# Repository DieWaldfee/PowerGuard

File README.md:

# PowerGuard
PowerGuard-Platine und Software zur Sicherheitsüberwachung einer Heizstabsteuerung

**zugehörige Repositories**<br>
- PowerGuard (dieses Repository)
- Heizstabsteuerung (Steuerungsplatine <a href="https://github.com/DieWaldfee/Heizstabsteuerung"> Link </a>)
- Heizstab_ioBroker (Ansteuerungs-Blockly - ein MQTT-Broker wird benötigt - Link)

**Funktion:** <br>
Der ESP32 steuert 2 Temperatursensoren (DS18B20) an und liest diese aus. Die beiden Sensoren sollen am höchsten Punkt des Pufferspeichers der Heizung angebracht werden, in dem auch der elektrische Heizstab eingeschraubt ist. 
Die beiden Werte werden einerseits verglichen und andererseits benutzt, um die Pufferspeichertemperatur zu überwachen. Liegt die Temperatur zu hoch, dann ist zu viel Energie im Pufferspeicher und vermutlich ist der Heizstab dafür ursächlich -> der Heizstabsteuerung wird der Strom abgeschalten. Dies stellt eine unabhängige Sicherungsfunktion dar, das jedweder Fehler im Heizstabsystem behandelt und die Anlage in den sicheren Zustand überführt (d.h. aus).<p>
Der PowerGuard hat 2 Möglichkeiten dies zu tun: <br>
(1) die 5V Versorgung des ESP32 der Heizstabsteuerung abzuschalten -> die Relais werden nicht mehr angesteuert - unabhängig vom Fehlerbild. <br>
(2) die 12V Versorgungsspannung der Lastschaltrelais (SSR siehe Heizstabsteuerung) wird abgeschaltet -> die Heizstabsteuerung bleibt aktiv, kann aber nichts mehr schalten. <p>
Die Kommunikation mit dem ESP32 wird über WiFi abgewickelt und über das Protokoll MQTT umgesetzt. Es stehen mehrere Befehle zur Verfügung, die ebenfalls via MQTT an den ESP gesendet werden kann. Neben "restart" / "reboot" (führt zu einem Neustart des ESP32) kann die ganze Konfiguration und der debug-Level angepasst werden. Alle Anpassungen sind nach einem Neustart verloren, da diese nicht permanent gespeichert werden. Befehle werden unter der MQTT-Hierarchie in folgendem Ort empfangen: `SmartHome/Keller/Heizung/ESP32_PowerGuard/command` (MQTT_SERIAL_RECEIVER_COMMAND)

**Entwicklungsumgebungen:** <br>
Die aktuelle Software (V2.x) für den ESP32 wird mit **PlatformIO** entwickelt (z. B. in VS Code mit dem PlatformIO-Plugin). Die Konfiguration des Projekts befindet sich in der Datei `platformio.ini`; Compilieren und Flashen erfolgen direkt über PlatformIO.<br>
Die historische Erstversion (V1.0) wurde in der **Arduino-IDE** erstellt und ist im Unterordner `V1.0/` archiviert.<br>
Die Platine (PCB) habe ich in Eagle von AutoCAD modelliert. Für Maker gibt es eine kostenfreie Version. Die CAM-Daten (PCB-Produktionsdaten), sowie die BOM (Stückliste) sind ebenfalls aus Eagle ausgegeben.
Eine Übersichtsversion der Platine ist mit Fritzing umgesetzt und enthält auch einige Notizen zur Pinbelegung.<br>

**benötigte Umgebung:** <br>
- ioBroker zur Ansteuerung (geht natürlich auch mit anderen SmartHome-Systemen, solange diese MQTT sprechen können)
- ioBroker MGTT-Adapter
- MQTT-Broker: z.B. mosquitto unter Linux/Debian/Raspian...
- 230V Stromversorgung oder alternativ eine 5V Versorgung über z.B. ein USB-Ladegerät (muss 2 ESP32 sicher versorgen können -> 2A reicht völlig aus) oder über die Schraubklemmen anderweitig versorgt.

### Abhängigkeiten (PlatformIO / `platformio.ini`):
OneWire:_______________PaulStoffregen/OneWire (git-master) – v2.3.7 inkompatibel mit ESP-IDF 5.x; v2.3.8 buggy<br>
DallasTemperature:_____milesburton/DallasTemperature v4.0.4<br>
PubSubClient:__________knolleary/PubSubClient v2.8<br>
WiFi.h / esp_task_wdt:_Espressif Arduino-Framework (via pioarduino platform-espressif32)<br>

### Board / Plattform (PlatformIO):
platform: pioarduino platform-espressif32 v55.03.38-1 (ESP-IDF 5.x)<br>
board: esp32dev<br>
framework: arduino<br>

**Hardware-Version (PCB V1.0 vs. V2.0):**<br>
In `platformio.ini` kann die Hardware-Version über ein Build-Flag gesetzt werden:<br>
```
build_flags = -DHARDWARE_VERSION=2   ; für PCB V2.0 (mit MSG-LED an Pin 22)
```
Ohne Build-Flag wird V1.0-Verhalten angenommen (kein MSG-LED, Blink auf OK-LED).<br>

| PIN | V1.0 | V2.0 |
|-----|------|------|
| 19  | LED OK (grün) | LED OK (grün) |
| 22  | – | LED MSG (gelb) |
| 23  | LED ERROR (rot) | LED ERROR (rot) |
| 25  | DS18B20 OneWire Bus | DS18B20 OneWire Bus |
| 32  | PHASE 5V (Heizstabsteuerung) | PHASE 5V (Heizstabsteuerung) |
| 18  | PHASE 12V (SSR-Relaisversorgung) | PHASE 12V (SSR-Relaisversorgung) |

**aktuelle Versionen:** <br>
- ESP-Software    V2.x (PlatformIO, `src/PowerGuard.cpp`)
- ESP-Software    V1.0 (Arduino IDE, archiviert in `V1.0/PowerGuard.ino`)
- PCB (Eagle) 	   V2.0
- CAM             V1.0
- BOM             V1.0
- Fritzing		      V1.1
 
Fokus der PCB V2.0 ist die Platine mit über einen PCB-Hersteller umzusetzen.
Die CAM-Datei ist passend für https://jlcpcb.com. Stand 03.11.2023 ist die Platine für 2$ (5 St.) bestellbar.
In der BOM findet sich die Stückliste für die Bestückung wieder.

Zugehöriges Projekt: https://github.com/users/DieWaldfee/projects/1

**Installation:**
* Zugangsdaten in `/src/secrets.h` eintragen (Hostname, WLAN-SSID, WLAN-Passwort, MQTT-Server, MQTT-Port, MQTT-User, MQTT-Passwort)
* Hardware-Version in `platformio.ini` als Build-Flag setzen (`-DHARDWARE_VERSION=2` für PCB V2.0, weglassen für V1.0)
* MQTT-Pfade sind in `src/PowerGuard.cpp` als `#define` hinterlegt und können dort angepasst werden<br>
&nbsp;&nbsp;&nbsp;
* Debug-Level kann via MQTT-Befehl `debug=0` … `debug=3` zur Laufzeit gesetzt werden (0 = Boot only; 1 = Basic; 2 = Advanced; 3 = Absolut); alternativ im Quellcode in Zeile 14 von `src/PowerGuard.cpp`
* ESP-Software wird über PlatformIO compiliert und auf das „ESP32 Dev Kit V4" geflasht.
* Platine entweder via Eagle an PCB-Hersteller übermitteln, oder das fertige CAM-File über die Anbieter-Webseite senden. (z.B. an https://jlcpcb.com)
* Platine bestücken + ESP und Level-Shifter (3.3V <-> 5V) aufsetzen.
* Relais anschließen.
* 12V Versorgung der Heizstabsteuerung wird über LED-Treiber realisiert.

### MQTT-Steuerbefehle

Befehle werden auf dem Topic **`SmartHome/Keller/Heizung/ESP32_PowerGuard/command`** empfangen.<br>
Bestätigungen erscheinen auf **`SmartHome/Keller/Heizung/ESP32_PowerGuard/ac`**.

| Befehl | Beschreibung | Antwort (ac-Topic) |
|--------|-------------|---------------------|
| `Test` | Verbindungstest | `Test OK` |
| `debug=0` … `debug=3` | Debug-Level setzen (0=Boot only, 1=Basic, 2=Advanced, 3=Absolut) | `debug=X umgesetzt` |
| `panicMode=0` | Panic-Modus zurücksetzen; Heizstabsteuerung neu starten (wenn thermalLimit=0) | `panicMode=0 umgesetzt` |
| `panicMode=1` | Panic-Abschaltung auslösen (5V + 12V aus) | `panicMode=1 umgesetzt` |
| `hardwareError=0` | Hardware-Fehler-Flag zurücksetzen | `hardwareError=0 umgesetzt` |
| `hardwareError=1` | Hardware-Fehler setzen → Panic-Abschaltung | `hardwareError=1 umgesetzt` |
| `thermalLimit=0` | Thermisches Limit zurücksetzen; Heizstabsteuerung neu starten (wenn panicMode=0 und hardwareError=0) | `thermalLimit=0 umgesetzt` |
| `thermalLimit=1` | Thermische Abschaltung auslösen (12V aus) | `thermalLimit=1 umgesetzt` |
| `tempLimit=<Wert>` | Abschalttemperatur 12V [°C] (Standard: 90,0) | `tempLimit=<Wert> umgesetzt` |
| `tempMaxLimit=<Wert>` | Panic-Abschalttemperatur 5V+12V [°C] (Standard: 95,0) | `tempMaxLimit=<Wert> umgesetzt` |
| `tempReconnect=<Wert>` | Wiedereinschalttemperatur [°C] (Standard: 80,0) | `tempReconnect=<Wert> umgesetzt` |
| `deltaT=<Wert>` | Max. zulässige Differenz zwischen den beiden Sensoren [K] (Standard: 2,0) | `deltaT=<Wert> umgesetzt` |
| `minTemp=<Wert>` | Untere Plausibilitätsgrenze [°C] (Standard: 10,0) | `minTemp=<Wert> umgesetzt` |
| `maxTemp=<Wert>` | Obere Plausibilitätsgrenze [°C] (Standard: 100,0) | `maxTemp=<Wert> umgesetzt` |
| `restart` oder `reboot` | ESP32 neu starten (Ausgänge werden vorher abgeschaltet) | `reboot in einer Sekunde!` |

> **Hinweis:** Alle Parameteränderungen sind flüchtig und gehen nach einem Neustart verloren.

### MQTT-Statustopics (veröffentlicht, alle 60 s)

Basis-Pfad: `SmartHome/Keller/Heizung/ESP32_PowerGuard/`

| Topic (relativ zum Basis-Pfad) | Inhalt | Retain |
|-------------------------------|--------|--------|
| `status` | Online-Status: `true` / `false` (LWT) | ja |
| `ac` | Befehlsbestätigungen | nein |
| `error` | Fehlermeldungen / Reconnect-Infos | ja |
| `Temperatur/0/JSON` | Sensor 0 komplett als JSON | nein |
| `Temperatur/0/Temperatur` | Temperatur Sensor 0 [°C] | nein |
| `Temperatur/0/ID` | Sensor-Index 0 | nein |
| `Temperatur/0/Adresse` | 1-Wire-Adresse Sensor 0 | nein |
| `Temperatur/0/Ort` | Ortsbezeichnung Sensor 0 | nein |
| `Temperatur/1/…` | Gleiche Subtopics für Sensor 1 | nein |
| `state/JSON` | Systemzustand komplett als JSON | nein |
| `state/panicMode` | Panic-Mode Flag (0/1) | nein |
| `state/thermalLimit` | Thermal-Limit Flag (0/1) | nein |
| `state/hardwareError` | Hardware-Fehler Flag (0/1) | nein |
| `state/lastError` | Letzter Fehler als Klartext | nein |
| `state/WiFi_Signal_Strength` | WiFi-Signalstärke [dBm] | nein |
| `state/WiFi_IP_Adress` | IP-Adresse | nein |
| `state/WiFi_MAC_Adress` | MAC-Adresse | nein |
| `config/JSON_0` | Konfigurationsparameter als JSON | nein |

**Bezugsquellen:**
* Platinennetzteil AC-05-3    <a href="https://www.azdelivery.de/products/copy-of-220v-zu-5v-mini-netzteil"> AZ-Delivery </a>
* Levelshifter (3.3V <-> 5V)  <a href="https://www.amazon.de/RUNCCI-YUN-Pegelwandler-Converter-BiDirektional-Mikrocontroller/dp/B082F6BSB5/ref=sr_1_2?__mk_de_DE=%C3%85M%C3%85%C5%BD%C3%95%C3%91&crid=45TPZ9B8CUP9&keywords=level+shifter&qid=1699045033&sprefix=level+shifter%2Caps%2C103&sr=8-2"> Amazon </a>
* Relais <a href="https://www.amazon.de/gp/product/B0B5816YJ7/ref=ppx_yo_dt_b_search_asin_image?ie=UTF8&th=1"> Amazon </a> oder <a href="https://www.az-delivery.de/products/relais-modul"> AZ Delivery </a>
* 12V LED-Treiber als Schaltspannung der SSR-Relais  <a href="https://www.amazon.de/gp/product/B082NLNCSB/ref=ppx_yo_dt_b_search_asin_image?ie=UTF8&psc=1"> Amazon </a>
* JST-Buchse <a href="https://www.amazon.de/gp/product/B0B2R99X99/ref=ppx_yo_dt_b_search_asin_title?ie=UTF8&psc=1"> Amazon </a>
* Klemmbuchse <a href="https://www.amazon.de/gp/product/B087RN8FDZ/ref=ppx_yo_dt_b_search_asin_title?ie=UTF8&th=1"> Amazon </a>
* Widerstände 4,7kOhm, 220 Ohm, 330 Ohm, Led grün, gelb und rot Amazon / eBay / Conrad...
* Temperatursensoren DS18B20 <a href="https://www.az-delivery.de/products/2er-set-ds18b20-mit-3m-kabel"> AZ Delivery </a>

**fertige Platine:**

(oberes Relais steuert +5V -> Heizstabsteuerung; unteres Relais steuert die 12V für die SSR-40-DA Lastschaltrelais)

**Haftungsausschluss**<br>
Deutsch: Dieses Projekt arbeitet mit Netzspannung (220 V) und darf ausschließlich von qualifiziertem Fachpersonal aufgebaut, installiert und betrieben werden. Durch die anliegende Spannung besteht Lebensgefahr! Fehler in Schaltung oder Software können zu Sachschäden (z. B. an Gebäude oder Heizung) oder zu gefährlichen Situationen für Leib und Leben führen. Nutzung auf eigene Gefahr – jegliche Haftung wird ausgeschlossen.
<br>
English: This project operates with mains voltage (220 V) and must only be assembled, installed, and operated by qualified professionals. The present voltage poses a risk of fatal electric shock! Errors in circuitry or software may cause property damage (e.g., to buildings or heating systems) or create life-threatening situations. Use at your own risk – any liability is disclaimed.

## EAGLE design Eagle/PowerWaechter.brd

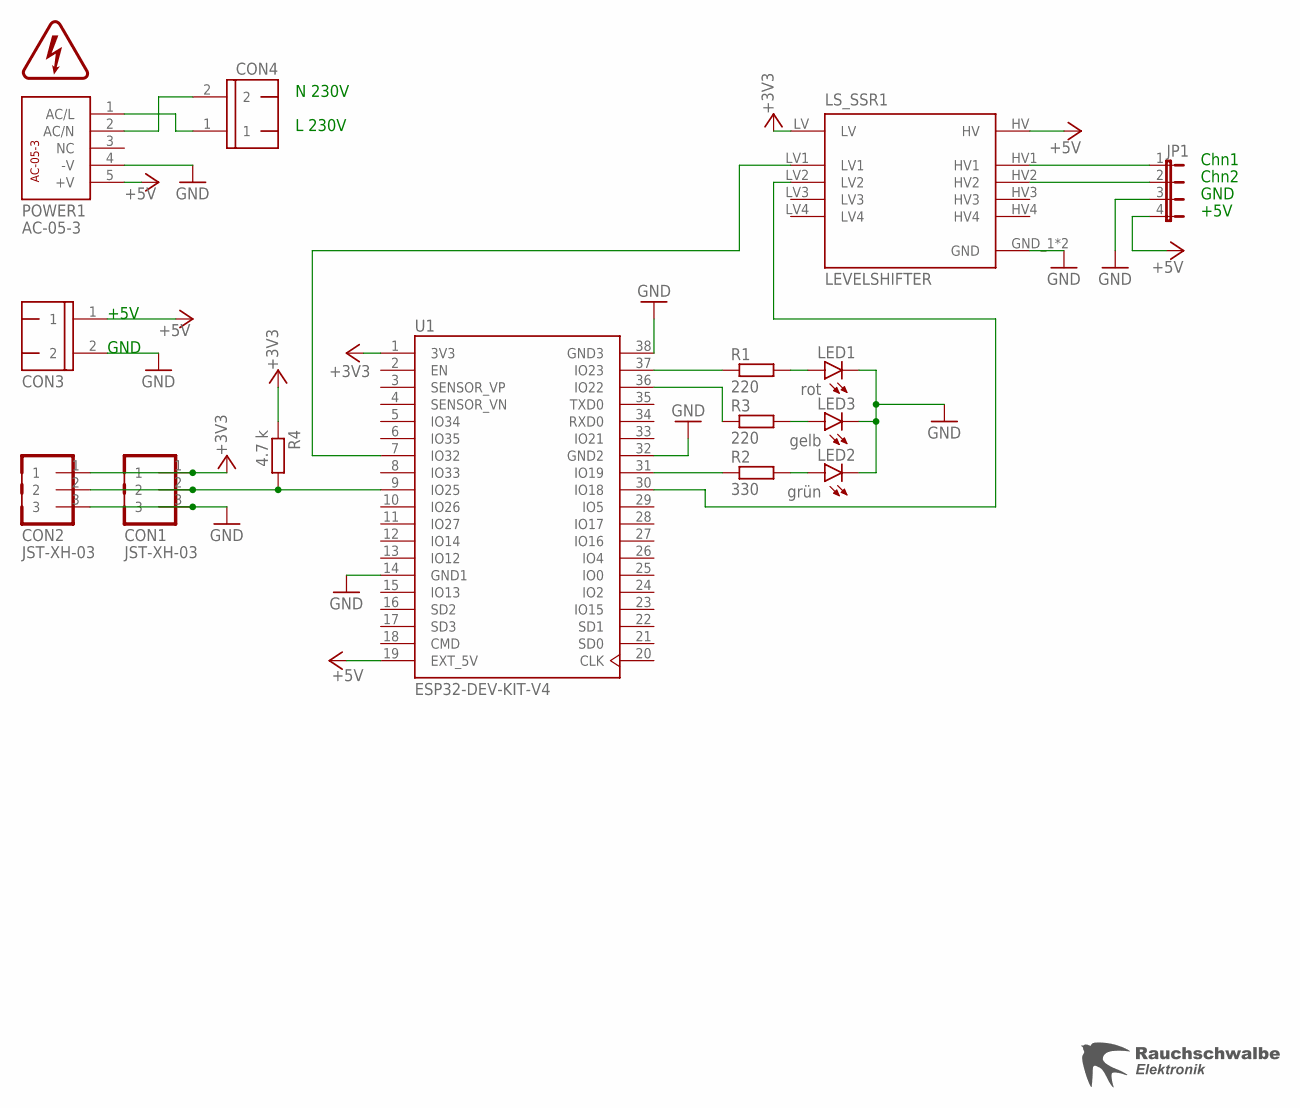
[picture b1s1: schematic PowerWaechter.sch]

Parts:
CON1, CON2: JST-XH-03
CON3, CON4: WAGO-500-2
JP1: JP4E; JP4
LED1: rot; LED3MM
LED2: grün; LED3MM
LED3: gelb; LED3MM
LS_SSR1: LEVELSHIFTER
POWER1: AC-05-3
R1, R3: 220; 0207/10
R2: 330; 0207/10
R4: 4.7 k; 0207/10
U1: ESP32-DEV-KIT-V4
U$1: WARNLABLE_BLITZ_KLEIN
U$2: LOGO_RAUCHSCHWALBE_KLEIN

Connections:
+3V3: CON1.1, CON2.1, LS_SSR1.LV, R4.1, U1.1 (3V3)
+5V: CON3.1, JP1.4, LS_SSR1.HV, POWER1.5 (+V), U1.19 (EXT_5V)
GND: CON1.3, CON2.3, CON3.2, JP1.3, LED1.K (C), LED2.K (C), LED3.K (C), LS_SSR1.GND_1 (GND), LS_SSR1.GND_2 (GND), POWER1.4 (-V), U1.14 (GND1), U1.32 (GND2), U1.38 (GND3)
unnamed: R1.1, U1.37 (IO23)
unnamed: LED3.A, R3.2
unnamed: R2.1, U1.31 (IO19)
unnamed: LED1.A, R1.2
unnamed: LED2.A, R2.2
unnamed: R3.1, U1.36 (IO22)
unnamed: LS_SSR1.LV1, U1.7 (IO32)
unnamed: CON1.2, CON2.2, R4.2, U1.9 (IO25)
unnamed: LS_SSR1.LV2, U1.30 (IO18)
unnamed: JP1.1, LS_SSR1.HV1
unnamed: JP1.2, LS_SSR1.HV2
PHASE_L: CON4.1, POWER1.1 (AC/L)
PHASE_N: CON4.2, POWER1.2 (AC/N)

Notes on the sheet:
GND
+5V
Chn1
Chn2
L 230V
N 230V

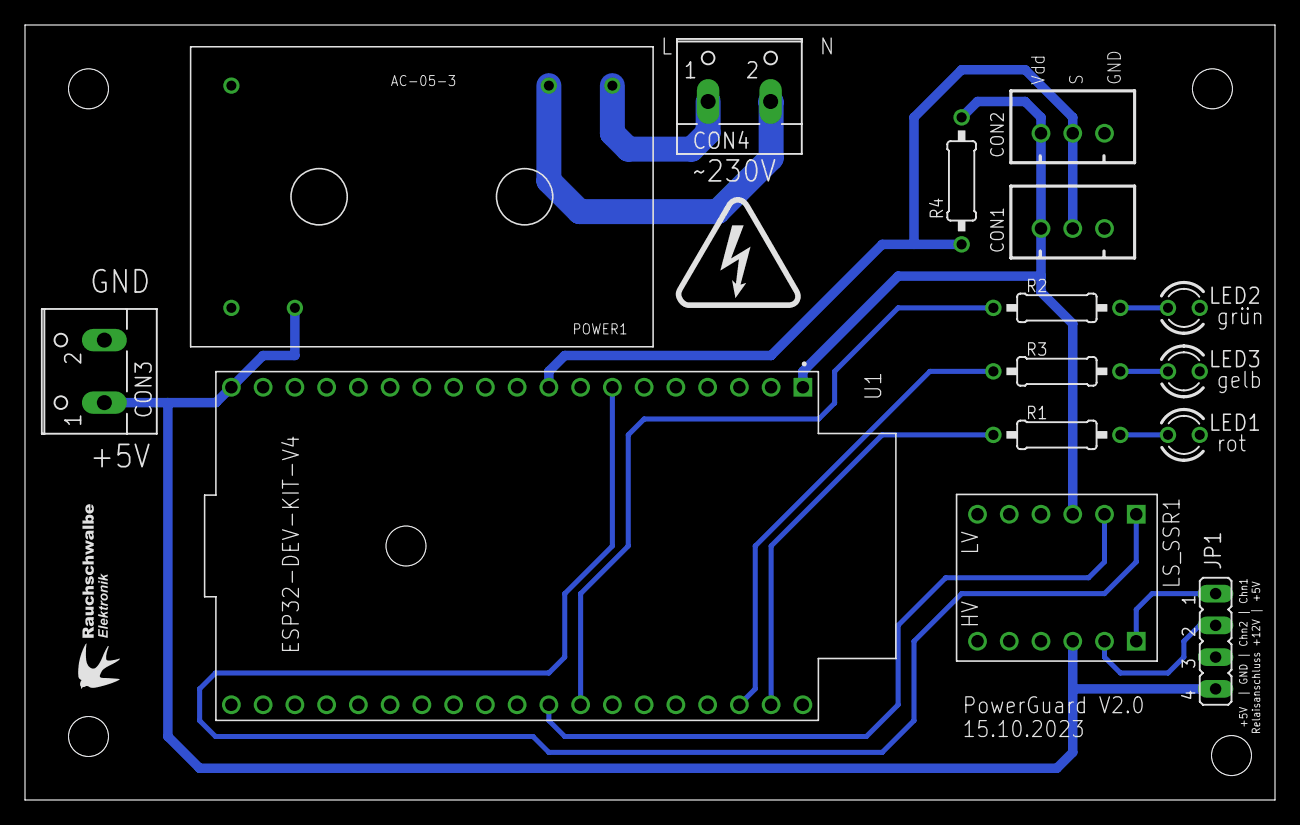
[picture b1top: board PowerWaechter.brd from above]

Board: 2 copper layers, 100.0 x 62.0 mm, 17 parts (0 on the bottom side), 16 nets.

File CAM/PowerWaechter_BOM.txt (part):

Stückliste PowerGuard 03.11.2023 15:11

Part    Value                    Device                   Package                  Description                                         AVAILABILITY CHECK_PRICES                                                                     DESCRIPTION                                                MF                                                                                         MP                MPN           OC_FARNELL OC_NEWARK PACKAGE POPULARITY PRICE PURCHASE-URL                                           SNAPEDA_LINK SPICEPREFIX                                                                      
CON1    JST-XH-03                JST-XH-03                JST-XH-03                                                                                                                                                                                                                                                                                                                                                                                                                                                                                                                                                           
CON2    JST-XH-03                JST-XH-03                JST-XH-03                                                                                                                                                                                                                                                                                                                                                                                                                                                                                                                                                           
CON3                             WAGO-500-2               WAGO-500-2               WAGO SCREW CLAMP                                                                                                                                                                                                                                                                                                          237-102       unknown    70K9898           32                                                                                                                                                                    
CON4                             WAGO-500-2               WAGO-500-2               WAGO SCREW CLAMP                                                                                                                                                                                                                                                                                                          237-102       unknown    70K9898           32                                                                                                                                                                    
JP1                              JP4E                     JP4                      JUMPER                                                                                                                                                                                                                                                                                                                                                               15                                                                                                                                                                    
LED1    rot                      LED3MM                   LED3MM                   LED                                                                                                                                                                                                                                                                                                                                                                  97                                                                                                                                                                    
LED2    grün                     LED3MM                   LED3MM                   LED                                                                                                                                                                                                                                                                                                                                                                  97                                                                                                                                                                    
LED3    gelb                     LED3MM                   LED3MM                   LED                                                                                                                                                                                                                                                                                                                                                                  97                                                                                                                                                                    
LS_SSR1 LEVELSHIFTER             LEVELSHIFTER             LEVELSHIFTER             Logic Level Converter - Bi-Direc Check availability In Stock                                                                                       BSS138 Logic-Level Translator Interface Evaluation Board  SparkFun                                                                                   BOB-12009                                            None               None  https://pricing.snapeda.com/search?q=BOB-12009&ref=eda                                                                                               
POWER1  AC-05-3                  AC-05-3                  AC-05-3                  AC-05-3                                                                                                                                                                                                                                                                                                                                                                                                                                                                                                                                    
R1      220                      R_10MM0207/10            0207/10                  RESISTOR, European symbol                                                                                                                                                                                                                                                                                                                                            81                                                                                   R                                                                                
R2      330                      R_10MM0207/10            0207/10                  RESISTOR, European symbol                                                                                                                                                                                                                                                                                                                                            81                                                                                   R                                                                                
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
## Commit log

2023-11-03 V1.0.2 überführen
2023-11-03 v2.0.0 überführt
2023-11-03 Update README.md
    Bilder erneuert
2023-11-03 Update README.md
    Platine als Bild ersetzt
2023-11-03 Update README.md
    BugFix Bild
2023-11-04 Update README.md
    Beschreibung ergänzt
    - Funktion
    - Entwicklungsumgebung
    - benötigte Umgebung
2023-11-04 Update README.md
    Bilder der fertigen Platine ergänzt
2023-11-04 Update README.md
    Versorgungsspannung über Klemme ergänzt
2023-11-04 Update README.md
    Link ergänzt zu Heizstabsteuerung
2023-11-17 V1.03 hinzugefügt
2023-11-17 Revert "V1.03 hinzugefügt"
    This reverts commit ff8b7150d76cacb5a83470fde4d5f4738e8275d2.
    Error rolback
2023-12-11 Update PowerGuard.ino
    reboot bei Verlust der MQTT-Verbindung (20 erfolglose reconnect-Versuche)
2023-12-11 Update PowerGuard.ino
    reboot nach 20 erfolglosen MQTT-Reconnects
2024-09-21 secrets.h add + Wifi strength in MQTT
2024-09-24 V1.06 InfoUpdate
    additional infos:
    - Wifi strength
    - error messages addes Temps
2024-09-29 Angleichung an V2.0.4
    assert problems fixed with wdt
2024-09-29 assert problems fixed with wdt
2025-05-29 V2.0.5 IP- and MAC-Adress in state
    V2.0.5 IP- and MAC-Adress in state
2025-05-29 analog V2.0.5
    Update analog V2.0.5
2025-07-26 Update secrets.h
    change name
2025-09-13 MQTT queued communication & safeReset integrated
2025-09-13 analog V2.1.0
2026-04-27 V3.0
2026-04-27 Add hardware version definition to secrets.h
2026-04-27 LED-Management for V1.0 & V2.0
2026-04-27 Revise README for ESP32 software and MQTT details
    Updated the README to reflect changes in the ESP32 software development environment and added details about MQTT commands and status topics.
